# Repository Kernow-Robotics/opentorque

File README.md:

# opentorque
Open source hardware and software for three-phase motors

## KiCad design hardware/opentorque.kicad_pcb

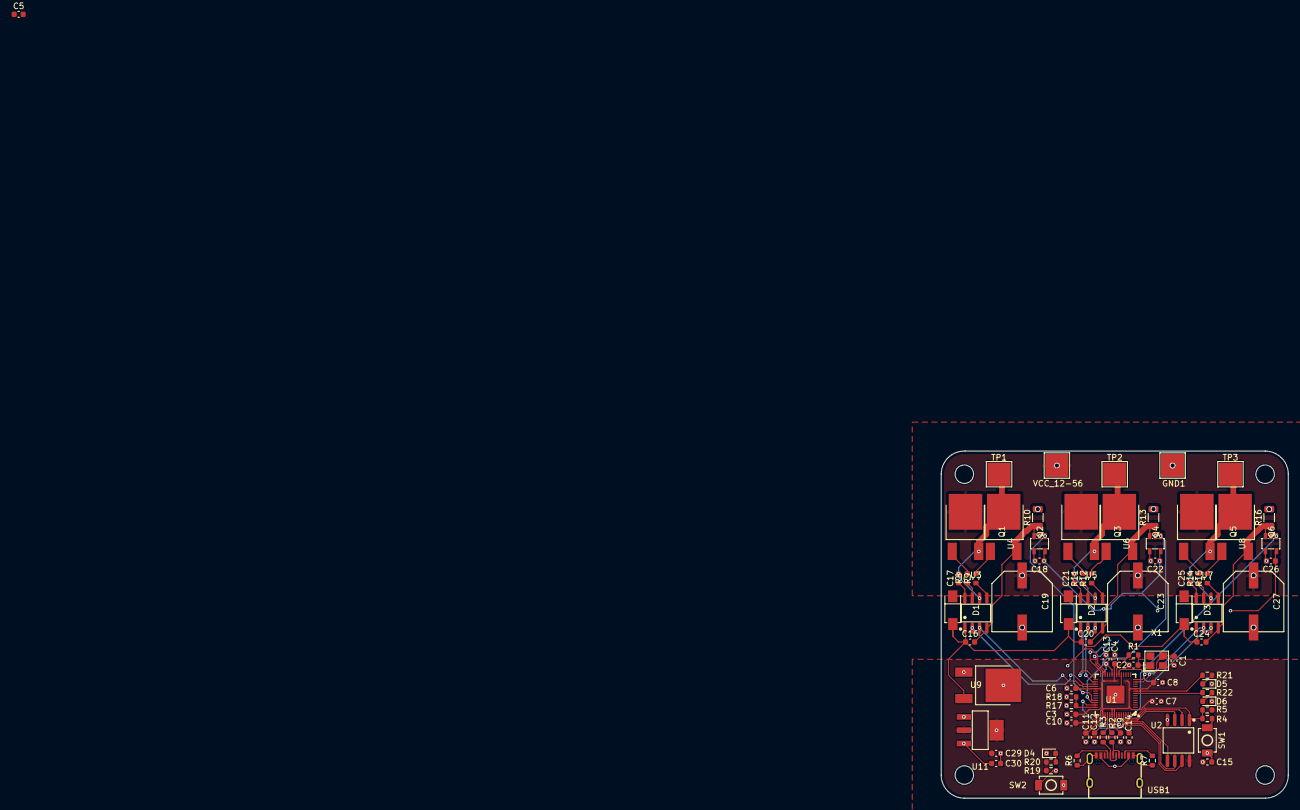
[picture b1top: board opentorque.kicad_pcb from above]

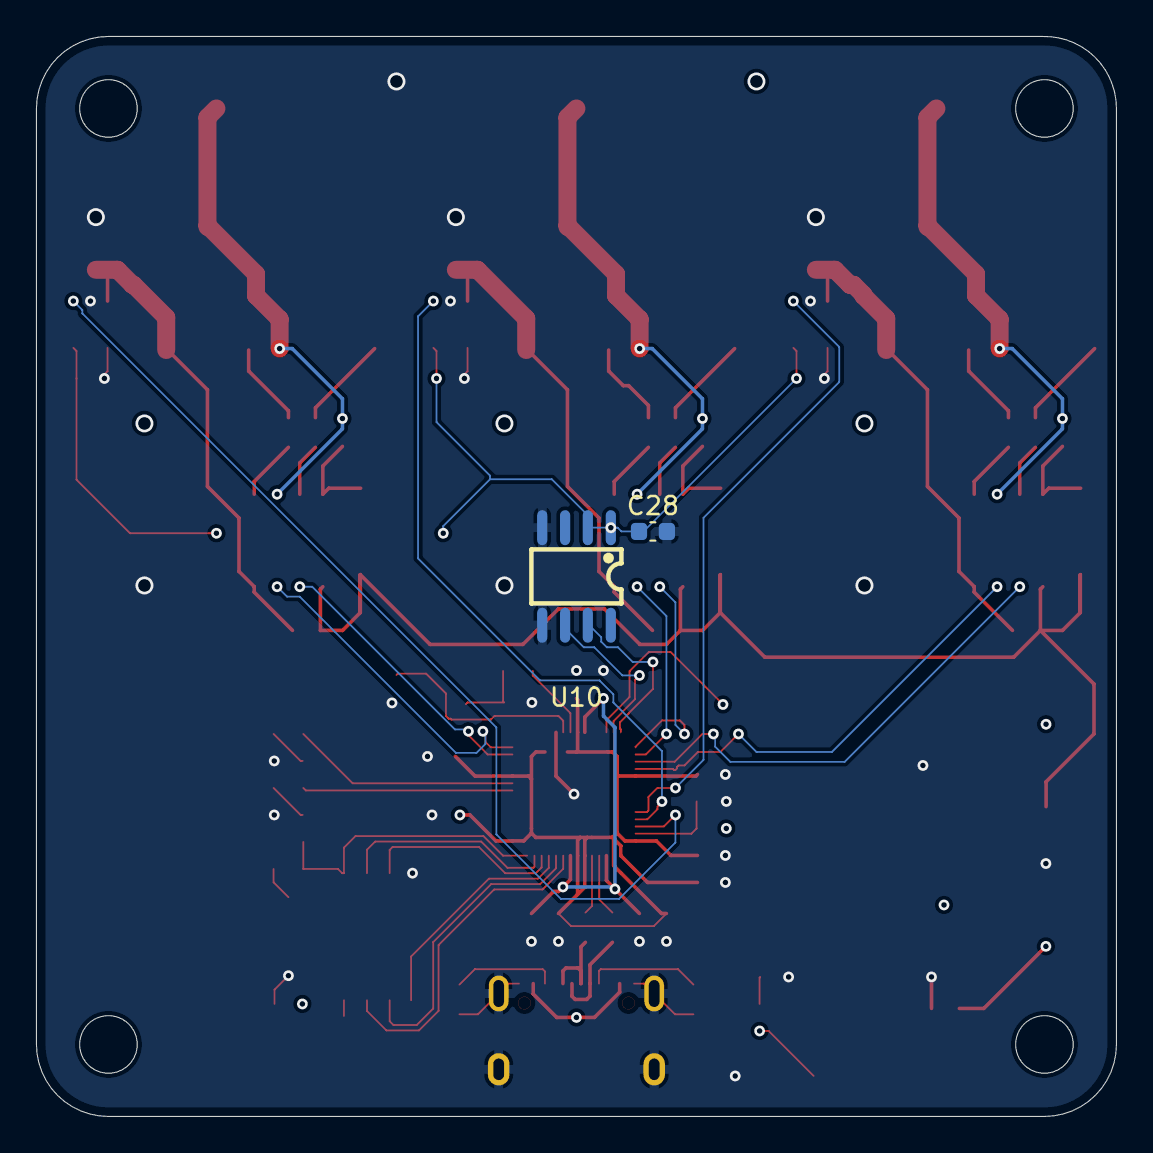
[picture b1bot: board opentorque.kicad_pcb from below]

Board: 4 copper layers, 60.0 x 60.0 mm, 84 parts (2 on the bottom side), 61 nets.

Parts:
C1, C2: 30p; C_0603_1608Metric
C3, C4, C5, C6, C7, C8, C9, C10, C13, C14, C15, C16, C17, C18, C20, C21, C22, C24, C25, C26, C28, C29, C30: 100n; C_0603_1608Metric
C11, C12: 1u; C_0603_1608Metric
C19, C23, C27: RVT1J221M1010; CAP-SMD_BD10.0-L10.3-W10.3-FD
D1, D2, D3: SS14_C2837270; SMA_L4.3-W2.6-LS5.0-RD
D4, D5, D6: LED; LED_0603_1608Metric
GND1: TestPoint; TestPoint_Pad_4.0x4.0mm
Q1, Q2, Q3, Q4, Q5, Q6: 30N06_C5807887; TO-252-2_L6.6-W6.1-P4.57-LS9.9-BR-CW
R1, R4, R18, R19: 1k; R_0603_1608Metric
R2, R3, R8, R9, R11, R12, R14, R15: 27R; R_0603_1608Metric
R5: 10k; R_0603_1608Metric
R6, R7: 5k1; R_0603_1608Metric
R10, R13, R16: 1m; R_1206_3216Metric
R17: 20k; R_0603_1608Metric
R20, R21, R22: 68R; R_0603_1608Metric
SW1, SW2: TS-1088-AR02016; SW-SMD_L3.9-W3.0-P4.45
TP1, TP2, TP3: TestPoint; TestPoint_Pad_4.0x4.0mm
U1: RP2040; LQFN-56_L7.0-W7.0-P0.4-EP
U2: W25Q128JVSIQTR; SOIC-8_L5.3-W5.3-P1.27-LS8.0-BL
U3, U5, U7: SLM2003ECA-DG; SOIC-8_L4.9-W3.9-P1.27-LS6.0-BL
U4, U6, U8: INA180A3IDBVR; SOT-23-5_L3.0-W1.7-P0.95-LS2.8-BR
U9: UMW78M12; TO-252-2_L6.6-W6.1-P4.57-LS9.9-BR-CW
U10: AS5600-ASOT; SOIC-8_L5.0-W4.0-P1.27-LS6.0-BL
U11: AMS1117-3.3_C347222; SOT-223-4_L6.5-W3.5-P2.30-LS7.0-BR
USB1: TYPE-C 16PIN 2MD(073); USB-C-SMD_TYPE-C-6PIN-2MD-073
VCC_12-56: TestPoint; TestPoint_Pad_4.0x4.0mm
X1: X322512MSB4SI; CRYSTAL-SMD_4P-L3.2-W2.5-BL

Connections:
+3V3: C3.1, C4.1, C5.1, C6.1, C7.1, C8.1, C9.1, C10.1, C11.1, C15.1, C18.1, C22.1, C26.1, C28.1, C29.1, R5.1, R19.1, R20.1, U1.1 (IOVDD), U1.10 (IOVDD), U1.22 (IOVDD), U1.33 (IOVDD), U1.42 (IOVDD), U1.43 (ADC_AVDD), U1.44 (VREG_IN), U1.48 (USB_VDD), U1.49 (IOVDD), U2.8 (VCC), U4.5 (V+), U6.5 (V+), U8.5 (V+), U10.1 (VDD5V), U10.2 (VDD3V3), U11.2 (VOUT(TAB)), U11.4 (TAB)
+12V: C16.1, C20.1, C24.1, D1.2 (A), D2.2 (A), D3.2 (A), U3.1 (VCC), U5.1 (VCC), U7.1 (VCC), U9.3 (OUT)
/SCL: U1.28 (GPIO17), U10.7 (SCL)
/SDA: U1.27 (GPIO16), U10.6 (SDA)
/Vsense: R17.2, R18.1, U1.41 (GPIO29_ADC3)
/phasedriver U/AOUT: U1.38 (GPIO26_ADC0), U4.1 (OUT)
/phasedriver U/HIN: U1.31 (GPIO20), U3.2 (HIN)
/phasedriver U/LINN: U1.32 (GPIO21), U3.3 (~LIN)
/phasedriver V/AOUT: U1.39 (GPIO27_ADC1), U6.1 (OUT)
/phasedriver V/HIN: U1.29 (GPIO18), U5.2 (HIN)
/phasedriver V/LINN: U1.30 (GPIO19), U5.3 (~LIN)
/phasedriver W/AOUT: U1.40 (GPIO28_ADC2), U8.1 (OUT)
/phasedriver W/HIN: U1.13 (GPIO10), U7.2 (HIN)
/phasedriver W/LINN: U1.14 (GPIO11), U7.3 (~LIN)
/rp2040/1.1V: C12.1, C13.1, C14.1, U1.23 (DVDD), U1.45 (VREG_VOUT), U1.50 (DVDD)
/rp2040/DN: R3.1, U1.46 (USB_DM)
/rp2040/DP: R2.1, U1.47 (USB_DP)
/rp2040/GPIO6: R22.1, U1.8 (GPIO6)
/rp2040/GPIO7: R21.1, U1.9 (GPIO7)
/rp2040/QSPI_SCLK: U1.52 (QSPI_SCLK), U2.6 (CLK)
/rp2040/QSPI_SD0: U1.53 (QSPI_SD0), U2.5 (DI)
/rp2040/QSPI_SD1: U1.55 (QSPI_SD1), U2.2 (DO)
/rp2040/QSPI_SD2: U1.54 (QSPI_SD2), U2.3 (IO2)
/rp2040/QSPI_SD3: U1.51 (QSPI_SD3), U2.7 (IO3)
/rp2040/QSPI_SS: R4.1, R5.2, U1.56 (QSPI_SS), U2.1 (~CS)
/rp2040/RUN: R19.2, SW2.2, U1.26 (RUN)
/rp2040/VBUS: C30.1, U11.3 (VIN), USB1.2 (VBUS), USB1.11 (VBUS)
/rp2040/XIN: C1.2, U1.20 (XIN), X1.3 (OSC2)
/rp2040/XOUT: R1.2, U1.21 (XOUT)
GND: C1.1, C2.1, C3.2, C4.2, C5.2, C6.2, C7.2, C8.2, C9.2, C10.2, C11.2, C12.2, C13.2, C14.2, C15.2, C18.2, C19.2, C22.2, C23.2, C26.2, C27.2, C28.2, C29.2, C30.2, D4.1 (K), D5.1 (K), D6.1 (K), GND1.1, R6.1, R7.1, R10.2, R13.2, R16.2, R18.2, SW1.1, SW2.1, U1.19 (TESTEN), U1.57 (GND), U2.4 (GND), U4.2 (GND), U4.4 (IN-), U6.2 (GND), U6.4 (IN-), U8.2 (GND), U8.4 (IN-), U9.2 (GND), U10.4 (GND), U10.5 (PGO), U11.1 (ADJ(GND)), USB1.1 (GND), USB1.12 (GND), USB1.13 (SHELL), USB1.14 (SHELL), X1.2 (GND), X1.4 (GND)
unnamed: C17.1, D1.1 (C), U3.8 (VB)
unnamed: C21.1, D2.1 (C), U5.8 (VB)
unnamed: C25.1, D3.1 (C), U7.8 (VB)
unnamed: D4.2 (A), R20.2
unnamed: D5.2 (A), R21.2
unnamed: D6.2 (A), R22.2
unnamed: Q1.1 (G), R8.2
unnamed: C17.2, Q1.3 (S), Q2.2 (D), TP1.1, U3.6 (VS)
unnamed: Q2.1 (G), R9.2
unnamed: C16.2, Q2.3 (S), R10.1, U3.4 (COM), U4.3 (IN+)
unnamed: Q3.1 (G), R11.2
unnamed: C21.2, Q3.3 (S), Q4.2 (D), TP2.1, U5.6 (VS)
unnamed: Q4.1 (G), R12.2
unnamed: C20.2, Q4.3 (S), R13.1, U5.4 (COM), U6.3 (IN+)
unnamed: Q5.1 (G), R14.2
unnamed: C25.2, Q5.3 (S), Q6.2 (D), TP3.1, U7.6 (VS)
unnamed: Q6.1 (G), R15.2
unnamed: C24.2, Q6.3 (S), R16.1, U7.4 (COM), U8.3 (IN+)
unnamed: R4.2, SW1.2
unnamed: R8.1, U3.7 (HO)
unnamed: R9.1, U3.5 (LO)
unnamed: R11.1, U5.7 (HO)
unnamed: R12.1, U5.5 (LO)
unnamed: R14.1, U7.7 (HO)
unnamed: R15.1, U7.5 (LO)
unnamed: R6.2, USB1.4 (CC1)
unnamed: R7.2, USB1.10 (CC2)
unnamed: R3.2, USB1.5 (DN2), USB1.7 (DN1)
unnamed: R2.2, USB1.6 (DP1), USB1.8 (DP2)
unnamed: C2.2, R1.1, X1.1 (OSC1)
VCC: C19.1, C23.1, C27.1, Q1.2 (D), Q3.2 (D), Q5.2 (D), R17.1, U9.1 (IN), VCC_12-56.1

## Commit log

2026-02-02 Add KiCad project files
2026-02-06 Add initial phase driver circuitry
2026-02-07 Arrange components
2026-02-13 Add more routing
2026-03-26 Fix BOOTSEL resistors and add reset button
2026-03-27 Change logic supply to come from VBUS
2026-03-27 Add LEDs and expand copper pours
2026-03-30 Improve trace widths and decoupling
    This should improve system stability
2026-03-30 Clean up schematic
2026-03-30 Improve schematic clarity
